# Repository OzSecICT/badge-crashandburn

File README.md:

# OzSec 2025 Badge: CRASHANDBURN
This is the git repo for the code and supporting documents for the OzSec 2025 badge, codename CRASHANDBURN.

This badge will be built in MicroPython on an RP2040 or RP2350, and support multiple minigames.

This repo is currently a work in progress as we start planning how to lay out the badge firmware.

## Contributing
You will need a few things to help develop the badge firmware:
- Visual Studio Code
- VS Code Extensions: Python, Pylance
- Python 3.12+
- mpremote 1.24+

Install Python, and then install `mpremote`. Install VS Code, and clone this repository. Open the repo in VS Code and install the recommended extensions.

Currently the badge firmware is developed with a Raspberry Pi Pico 2 on a breadboard. If you want to see the code, obtain one and follow these steps to get it setup:
- Plug in drive while holding BOOTSEL and use the flash script or VS Code Task to flash firmware. 
    - In VS Code, hit Ctrl+Shift+P or Cmd+Shift+P and choose `Tasks: Run Task` followed by `Flash MicroPython Firmware`.
- After you make changes to the code, hit Ctrl+Shift+B or Cmd+Shift+B to automatically upload the code and reset the device.

## Folder Structure
`.vscode` has the needed VS Code settings for recommended plugins, tasks, and settings for Pylance.

`firmware` has the MicroPython firmware, so everyone uses the same one.

`scripts` contains supporting scripts, such as flash and upload scripts. These are used by VS Code Tasks.

`source` is the MicroPython source files uploaded to the device.

`typings` contains Python typings for MicroPython. It stops the red squigglies.

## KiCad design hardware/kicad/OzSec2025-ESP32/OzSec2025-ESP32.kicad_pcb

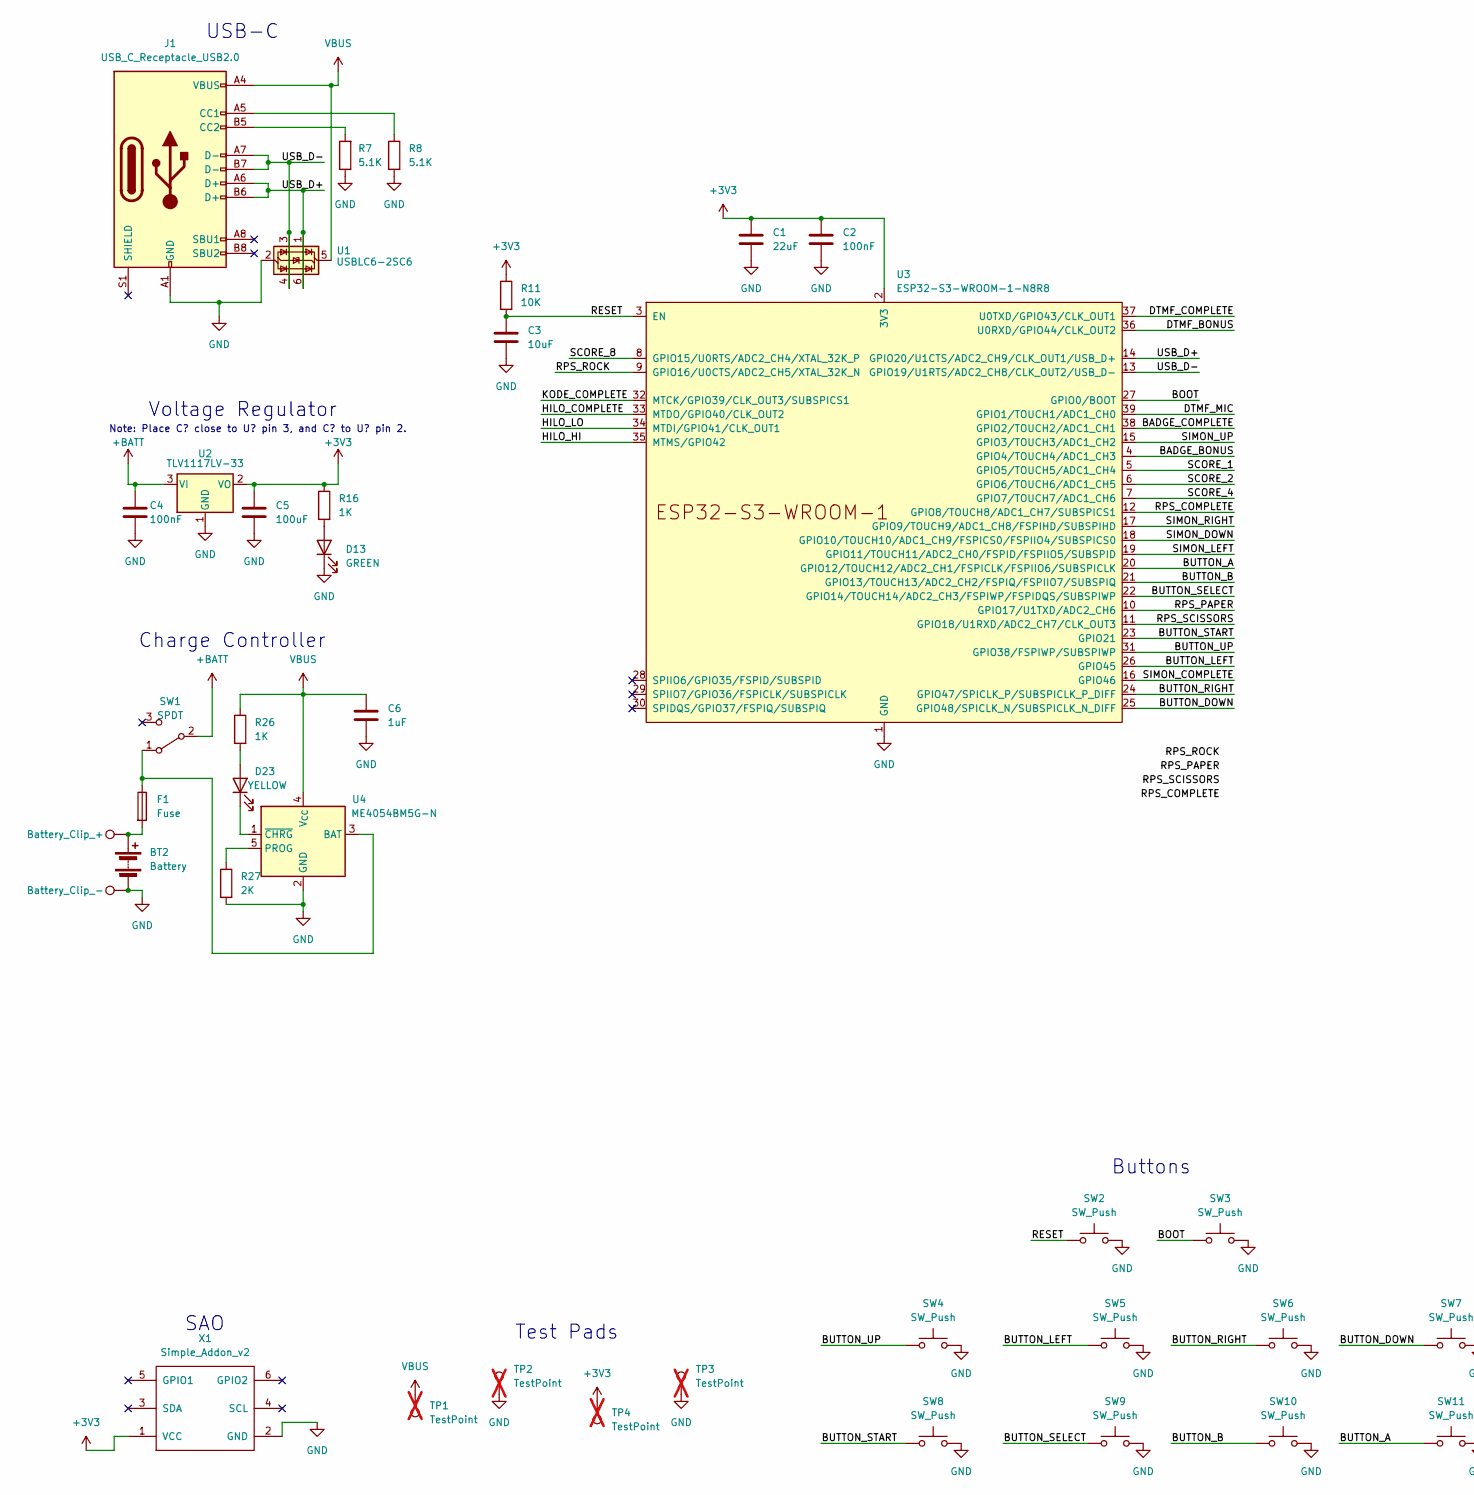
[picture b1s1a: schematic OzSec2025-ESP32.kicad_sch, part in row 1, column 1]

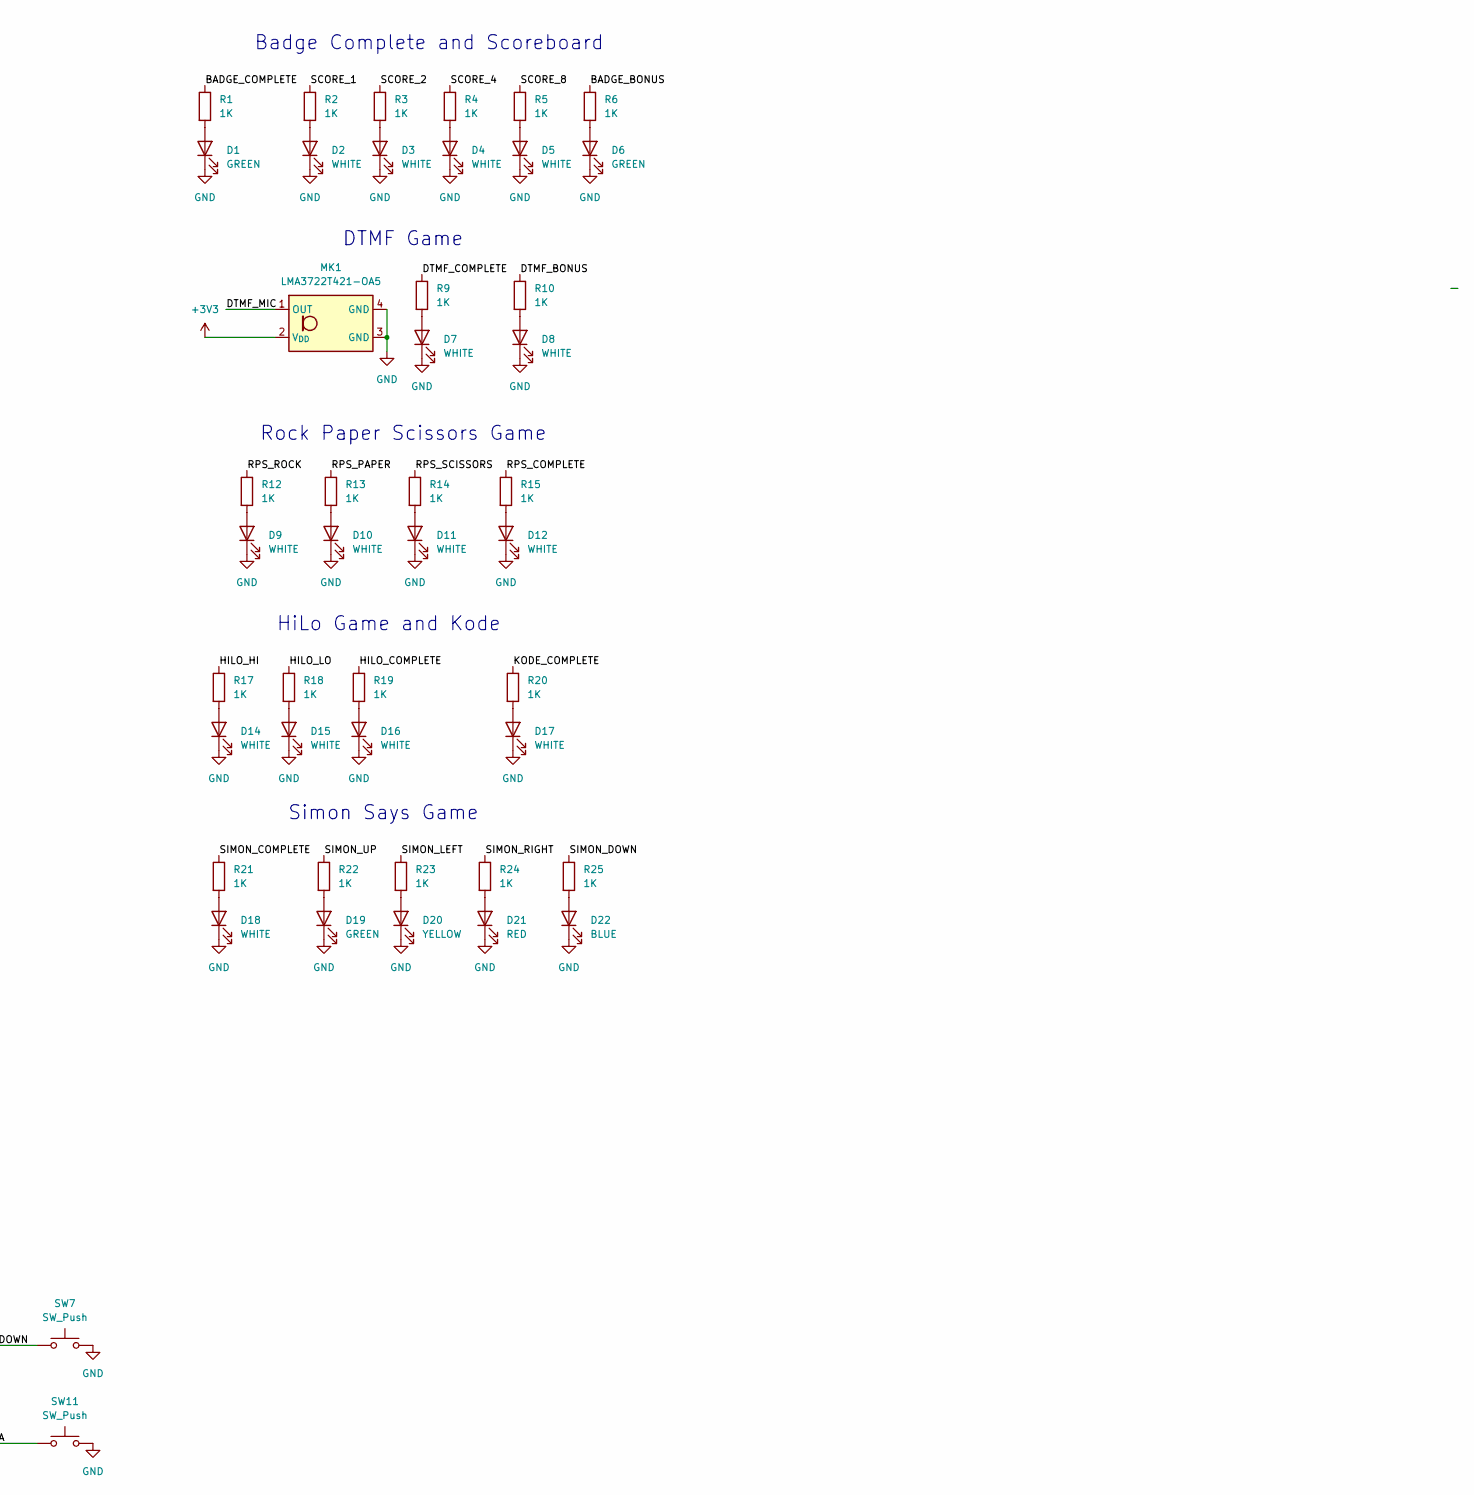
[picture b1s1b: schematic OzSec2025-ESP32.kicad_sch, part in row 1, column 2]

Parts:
BT1: Battery_Clip_+; MY-AA-04; LCSC C2979179
BT2: Battery; MY-AA-04; LCSC C2979179
BT3: Battery_Clip_-; MY-AA-04; LCSC C2979179
C1: 22uF; C_0805_2012Metric_Pad1.18x1.45mm_HandSolder; LCSC C45783
C2, C4: 100nF; C_0805_2012Metric_Pad1.18x1.45mm_HandSolder; LCSC C49678
C3: 10uF; C_0805_2012Metric_Pad1.18x1.45mm_HandSolder; LCSC C15850
C5: 100uF; C_1206_3216Metric_Pad1.33x1.80mm_HandSolder; LCSC C15008
C6: 1uF; C_0805_2012Metric_Pad1.18x1.45mm_HandSolder; LCSC C28323
D1, D6, D13, D19: GREEN; LED_0805_2012Metric_Pad1.15x1.40mm_HandSolder; LCSC C2297
D2, D3, D4, D5, D7, D8, D9, D10, D11, D12, D14, D15, D16, D17, D18: WHITE; LED_0805_2012Metric_Pad1.15x1.40mm_HandSolder; LCSC C34499
D20, D23: YELLOW; LED_0805_2012Metric_Pad1.15x1.40mm_HandSolder; LCSC C2296
D21: RED; LED_0805_2012Metric_Pad1.15x1.40mm_HandSolder; LCSC C84256
D22: BLUE; LED_0805_2012Metric_Pad1.15x1.40mm_HandSolder; LCSC C2293
F1: Fuse; Fuse_1206_3216Metric_Pad1.42x1.75mm_HandSolder; LCSC C261957
J1: USB_C_Receptacle_USB2.0; USB_C_Receptacle_G-Switch_GT-USB-7010ASV; LCSC C2988369
MK1: LMA3722T421-OA5; LCSC C5373233
R1, R2, R3, R4, R5, R6, R9, R10, R12, R13, R14, R15, R16, R17, R18, R19, R20, R21, R22, R23, R24, R25, R26: 1K; R_0805_2012Metric_Pad1.20x1.40mm_HandSolder; LCSC C17513
R7, R8: 5.1K; R_0805_2012Metric_Pad1.20x1.40mm_HandSolder; LCSC C27834
R11: 10K; R_0805_2012Metric_Pad1.20x1.40mm_HandSolder; LCSC C17414
R27: 2K; R_0805_2012Metric_Pad1.20x1.40mm_HandSolder; LCSC C17604
SW1: SPDT; SW_SPDT_PCM12; LCSC C431541
SW2, SW3, SW4, SW5, SW6, SW7, SW8, SW9, SW10, SW11: SW_Push; SW_Push_1P1T_XKB_TS-1187A; LCSC C318884
TP1, TP4: TestPoint; TestPoint_Pad_1.5x1.5mm; not fitted
TP2, TP3: TestPoint; TestPoint_Pad_D1.5mm; not fitted
U1: USBLC6-2SC6; SOT-23-6; LCSC C2827654
U2: TLV1117LV-33; SOT-223-3_TabPin2; LCSC C15578
U3: ESP32-S3-WROOM-1-N8R8; ESP32-S3-WROOM-1; LCSC C2913201
U4: ME4054BM5G-N; TSOT-23-5; LCSC C478383
X1: Simple_Addon_v2; Simple_Addon_v2-BADGE-2x3; LCSC C2935983

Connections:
+3V3: C1.1, C2.1, C5.1, MK1.2 (V_{DD}), R11.1, R16.1, TP4.1, U2.2 (VO), U3.2 (3V3), X1.1 (VCC)
+BATT: C4.1, SW1.2 (B), U2.3 (VI)
/BADGE_BONUS: R6.1, U3.4 (GPIO4/TOUCH4/ADC1_CH3)
/BADGE_COMPLETE: R1.1, U3.38 (GPIO2/TOUCH2/ADC1_CH1)
/BOOT: SW3.1, U3.27 (GPIO0/BOOT)
/BUTTON_A: SW11.1, U3.20 (GPIO12/TOUCH12/ADC2_CH1/FSPICLK/FSPIIO6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)
/BUTTON_B: SW10.1, U3.21 (GPIO13/TOUCH13/ADC2_CH2/FSPIQ/FSPIIO7/S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)
/BUTTON_DOWN: SW7.1, U3.25 (GPIO48/SPICLK_N/SUBSPICLK_N_DIFF)
/BUTTON_LEFT: SW5.1, U3.26 (GPIO45)
/BUTTON_RIGHT: SW6.1, U3.24 (GPIO47/SPICLK_P/SUBSPICLK_P_DIFF)
/BUTTON_SELECT: SW9.1, U3.22 (GPIO14/TOUCH14/ADC2_CH3/FSPIWP/FSPIDQS/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)
/BUTTON_START: SW8.1, U3.23 (GPIO21)
/BUTTON_UP: SW4.1, U3.31 (GPIO38/FSPIWP/SUBSPIWP)
/DTMF_BONUS: R10.1, U3.36 (U0RXD/GPIO44/CLK_OUT2)
/DTMF_COMPLETE: R9.1, U3.37 (U0TXD/GPIO43/CLK_OUT1)
/DTMF_MIC: MK1.1 (OUT), U3.39 (GPIO1/TOUCH1/ADC1_CH0)
/HILO_COMPLETE: R19.1, U3.33 (MTDO/GPIO40/CLK_OUT2)
/HILO_HI: R17.1, U3.35 (MTMS/GPIO42)
/HILO_LO: R18.1, U3.34 (MTDI/GPIO41/CLK_OUT1)
/KODE_COMPLETE: R20.1, U3.32 (MTCK/GPIO39/CLK_OUT3/SUBSPICS1)
/RESET: C3.1, R11.2, SW2.1, U3.3 (EN)
/RPS_COMPLETE: R15.1, U3.12 (GPIO8/TOUCH8/ADC1_CH7/SUBSPICS1)
/RPS_PAPER: R13.1, U3.10 (GPIO17/U1TXD/ADC2_CH6)
/RPS_ROCK: R12.1, U3.9 (GPIO16/U0CTS/ADC2_CH5/XTAL_32K_N)
/RPS_SCISSORS: R14.1, U3.11 (GPIO18/U1RXD/ADC2_CH7/CLK_OUT3)
/SCORE_1: R2.1, U3.5 (GPIO5/TOUCH5/ADC1_CH4)
/SCORE_2: R3.1, U3.6 (GPIO6/TOUCH6/ADC1_CH5)
/SCORE_4: R4.1, U3.7 (GPIO7/TOUCH7/ADC1_CH6)
/SCORE_8: R5.1, U3.8 (GPIO15/U0RTS/ADC2_CH4/XTAL_32K_P)
/SIMON_COMPLETE: R21.1, U3.16 (GPIO46)
/SIMON_DOWN: R25.1, U3.18 (GPIO10/TOUCH10/ADC1_CH9/FSPICS0/FSPIIO4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)
/SIMON_LEFT: R23.1, U3.19 (GPIO11/TOUCH11/ADC2_CH0/FSPID/FSPIIO5/S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)
/SIMON_RIGHT: R24.1, U3.17 (GPIO9/TOUCH9/ADC1_CH8/FSPIHD/SUBSPIHD)
/SIMON_UP: R22.1, U3.15 (GPIO3/TOUCH3/ADC1_CH2)
/USB_D+: J1.A6 (D+), J1.B6 (D+), U1.1 (I/O1), U1.6 (I/O1), U3.14 (GPIO20/U1CTS/ADC2_CH9/CLK_OUT1/USB_D+)
/USB_D-: J1.A7 (D-), J1.B7 (D-), U1.3 (I/O2), U1.4 (I/O2), U3.13 (GPIO19/U1RTS/ADC2_CH8/CLK_OUT2/USB_D-)
GND: BT1.2, BT3.1, C1.2, C2.2, C3.2, C4.2, C5.2, C6.2, D1.1 (K), D2.1 (K), D3.1 (K), D4.1 (K), D5.1 (K), D6.1 (K), D7.1 (K), D8.1 (K), D9.1 (K), D10.1 (K), D11.1 (K), D12.1 (K), D13.1 (K), D14.1 (K), D15.1 (K), D16.1 (K), D17.1 (K), D18.1 (K), D19.1 (K), D20.1 (K), D21.1 (K), D22.1 (K), J1.A1 (GND), J1.A12 (GND), J1.B1 (GND), J1.B12 (GND), MK1.3 (GND), MK1.4 (GND), R7.1, R8.2, R27.2, SW2.2, SW3.2, SW4.2, SW5.2, SW6.2, SW7.2, SW8.2, SW9.2, SW10.2, SW11.2, TP2.1, TP3.1, U1.2 (GND), U2.1 (GND), U3.1 (GND), U3.40 (GND), U3.41 (GND), U4.2 (GND), X1.2 (GND)
unnamed: BT1.1, F1.2
unnamed: D1.2 (A), R1.2
unnamed: D2.2 (A), R2.2
unnamed: D3.2 (A), R3.2
unnamed: D4.2 (A), R4.2
unnamed: D5.2 (A), R5.2
unnamed: D6.2 (A), R6.2
unnamed: D7.2 (A), R9.2
unnamed: D8.2 (A), R10.2
unnamed: D9.2 (A), R12.2
unnamed: D10.2 (A), R13.2
unnamed: D11.2 (A), R14.2
unnamed: D12.2 (A), R15.2
unnamed: D13.2 (A), R16.2
unnamed: D14.2 (A), R17.2
unnamed: D15.2 (A), R18.2
unnamed: D16.2 (A), R19.2
unnamed: D17.2 (A), R20.2
unnamed: D18.2 (A), R21.2
unnamed: D19.2 (A), R22.2
unnamed: D20.2 (A), R23.2
unnamed: D21.2 (A), R24.2
unnamed: D22.2 (A), R25.2
unnamed: D23.2 (A), R26.2
unnamed: D23.1 (K), U4.1 (~CHRG)
unnamed: J1.A5 (CC1), R8.1
unnamed: J1.B5 (CC2), R7.2
unnamed: F1.1, SW1.1 (A), U4.3 (BAT)
unnamed: R27.1, U4.5 (PROG)
VBUS: C6.1, J1.A4 (VBUS), J1.A9 (VBUS), J1.B4 (VBUS), J1.B9 (VBUS), R26.1, TP1.1, U1.5 (VBUS), U4.4 (V_{CC})

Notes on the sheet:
USB-C
Charge Controller
Badge Complete and Scoreboard
Test Pads
DTMF Game
Voltage Regulator
SAO
HiLo Game and Kode
Note: Place C? close to U? pin 3, and C? to U? pin 2.
Buttons
Simon Says Game
Rock Paper Scissors Game

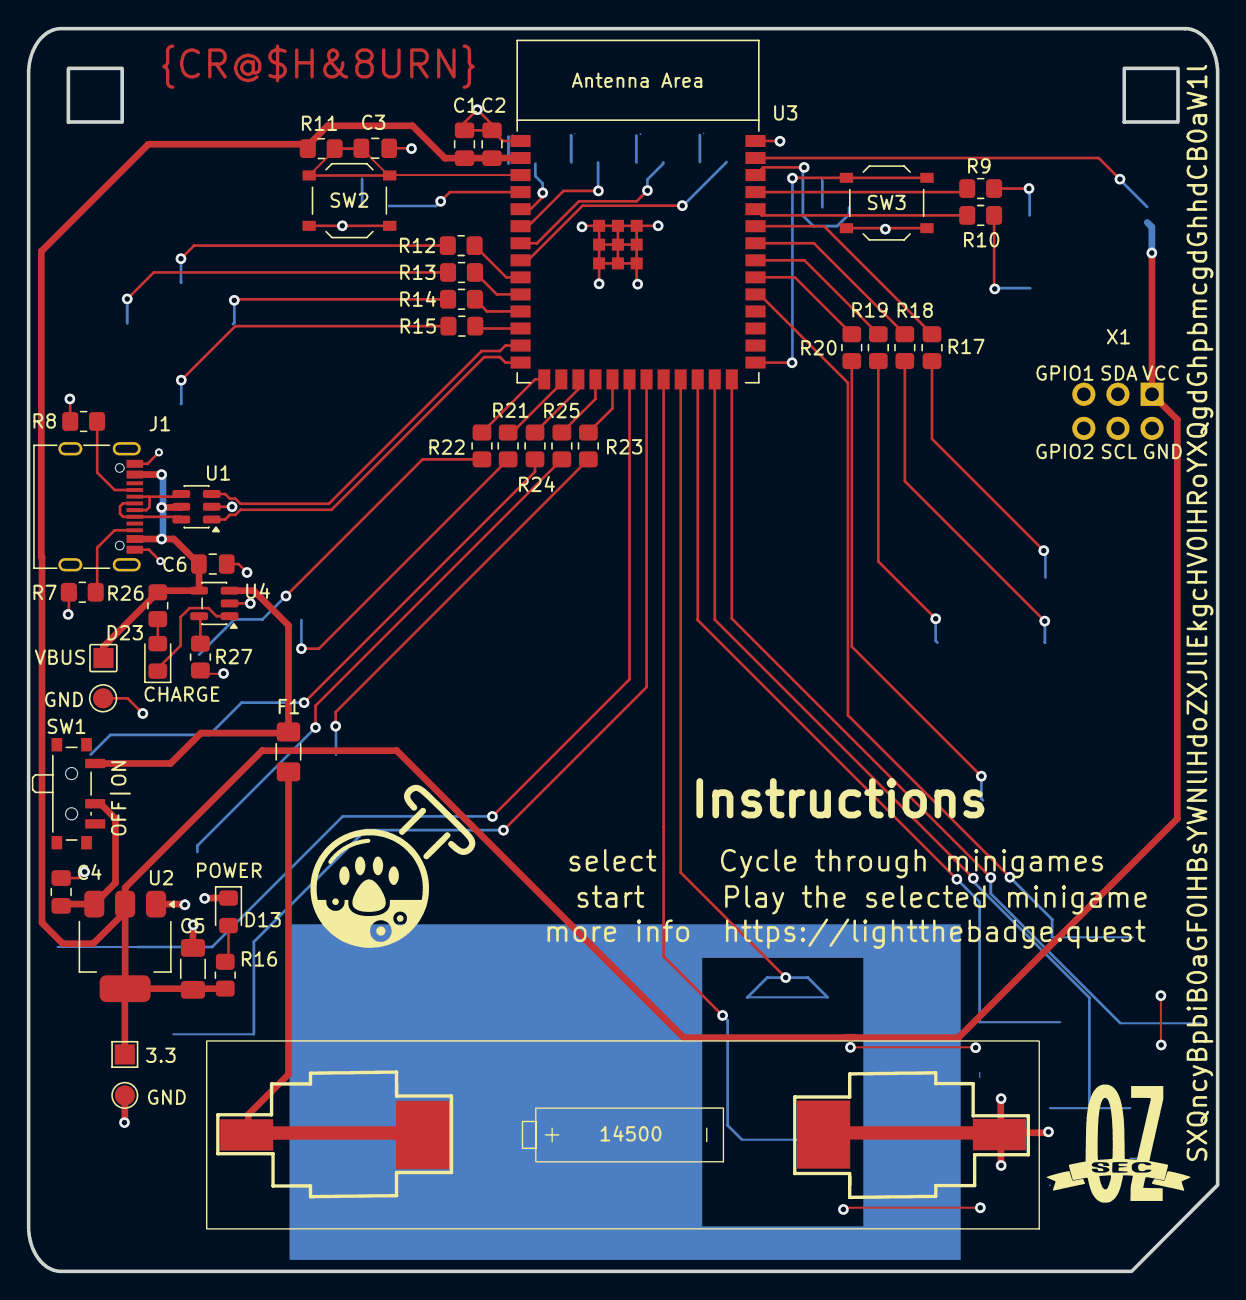
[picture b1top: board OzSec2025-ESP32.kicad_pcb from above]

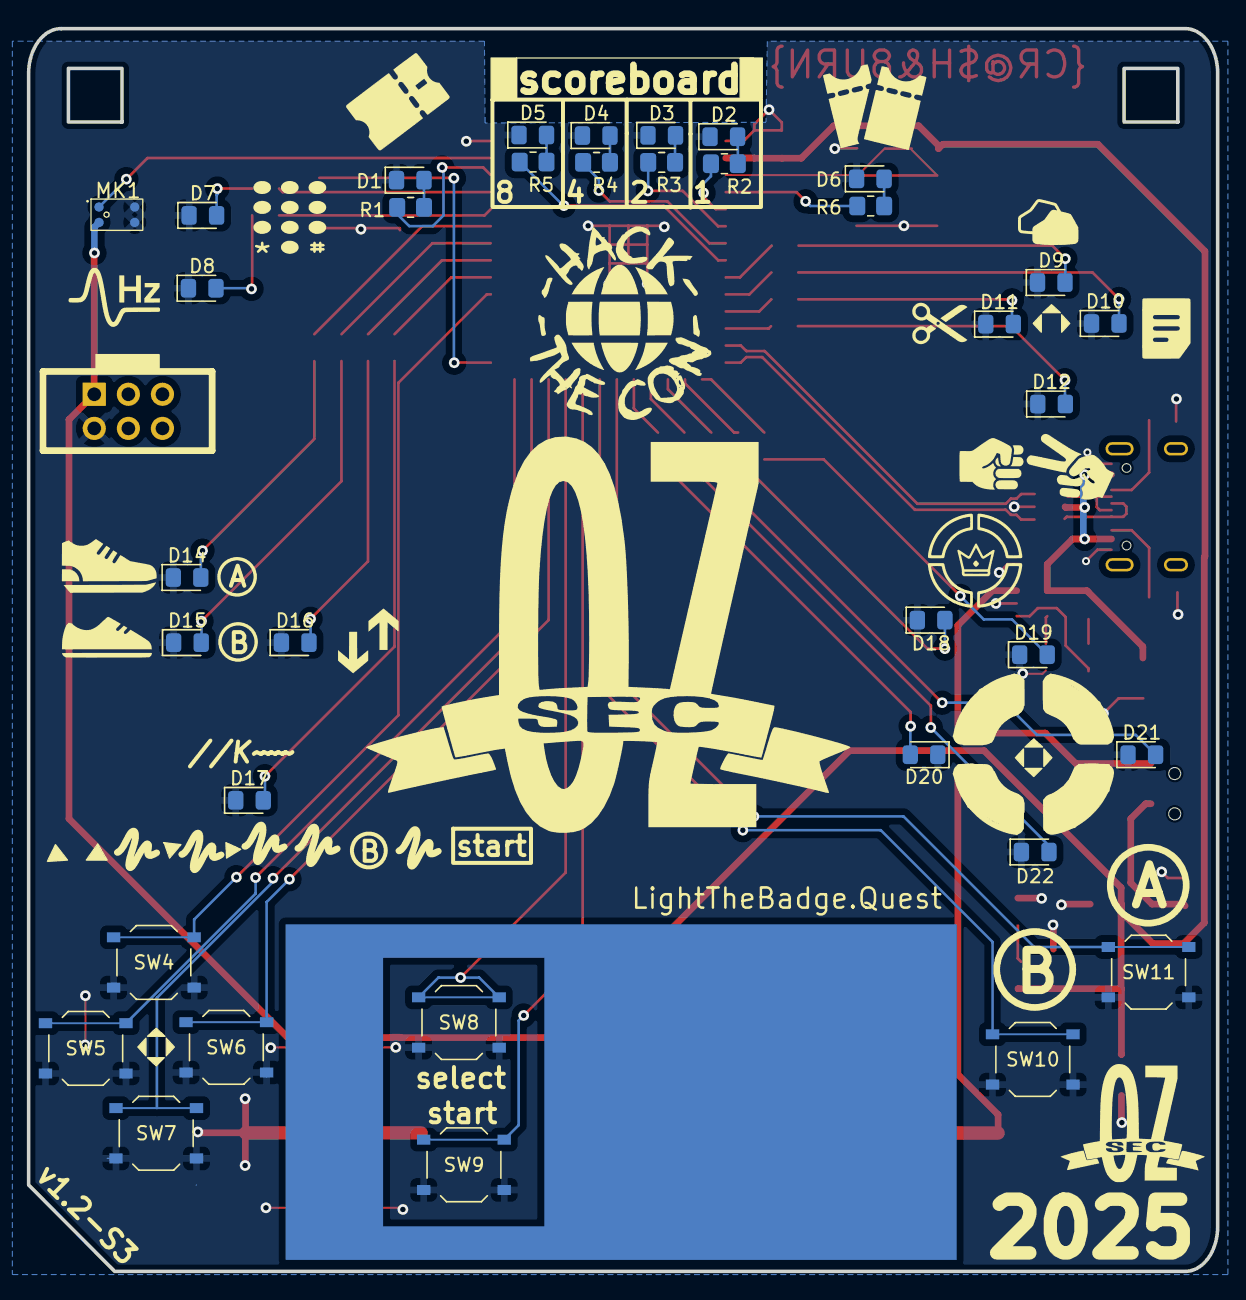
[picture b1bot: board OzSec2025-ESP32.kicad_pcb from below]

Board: 2 copper layers, 88.6 x 92.6 mm, 82 parts (37 on the bottom side), 67 nets.

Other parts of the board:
BATTERY: Battery; MY-AA-04_Silkscreen_Only

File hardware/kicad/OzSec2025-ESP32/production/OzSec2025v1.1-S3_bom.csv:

Designator,Footprint,Quantity,Value,LCSC Part #
BATTERY,MY-AA-04_Silkscreen_Only,1,Battery,C2979179
BT1,MY-AA-04,1,Battery_Clip_+,C2979179
BT3,MY-AA-04,1,Battery_Clip_-,C2979179
C1,0805,1,22uF,C45783
"C2, C4",0805,2,100nF,C49678
C3,0805,1,10uF,C15850
C5,1206,1,100uF,C15008
C6,0805,1,1uF,C28323
"D1, D13, D19, D6",0805,4,GREEN,C2297
"D10, D11, D12, D14, D15, D16, D17, D18, D2, D3, D4, D5, D7, D8, D9",0805,15,WHITE,C34499
"D20, D23",0805,2,YELLOW,C2296
D21,0805,1,RED,C84256
D22,0805,1,BLUE,C2293
F1,1206,1,Fuse,C261957
J1,USB_C_Receptacle_G-Switch_GT-USB-7010ASV,1,USB_C_Receptacle_USB2.0,C2988369
MK1,LMA3722T421-OA5,1,LMA3722T421-OA5,C5373233
"R1, R10, R12, R13, R14, R15, R16, R17, R18, R19, R2, R20, R21, R22, R23, R24, R25, R26, R3, R4, R5, R6, R9",0805,23,1K,C17513
R11,0805,1,10K,C17414
R27,0805,1,2K,C17604
"R7, R8",0805,2,5.1K,C27834
SW1,SW_SPDT_PCM12,1,SPDT,C431541
"SW10, SW11, SW2, SW3, SW4, SW5, SW6, SW7, SW8, SW9",SW_Push_1P1T_XKB_TS-1187A,10,SW_Push,C318884
U1,SOT-23-6,1,USBLC6-2SC6,C2827654
U2,SOT-223-3_TabPin2,1,TLV1117LV-33,C15578
U3,ESP32-S3-WROOM-1,1,ESP32-S3-WROOM-1-N8R8,C2913201
U4,TSOT-23-5,1,ME4054BM5G-N,C478383
X1,Simple_Addon_v2-BADGE-2x3,1,Simple_Addon_v2,C2935983

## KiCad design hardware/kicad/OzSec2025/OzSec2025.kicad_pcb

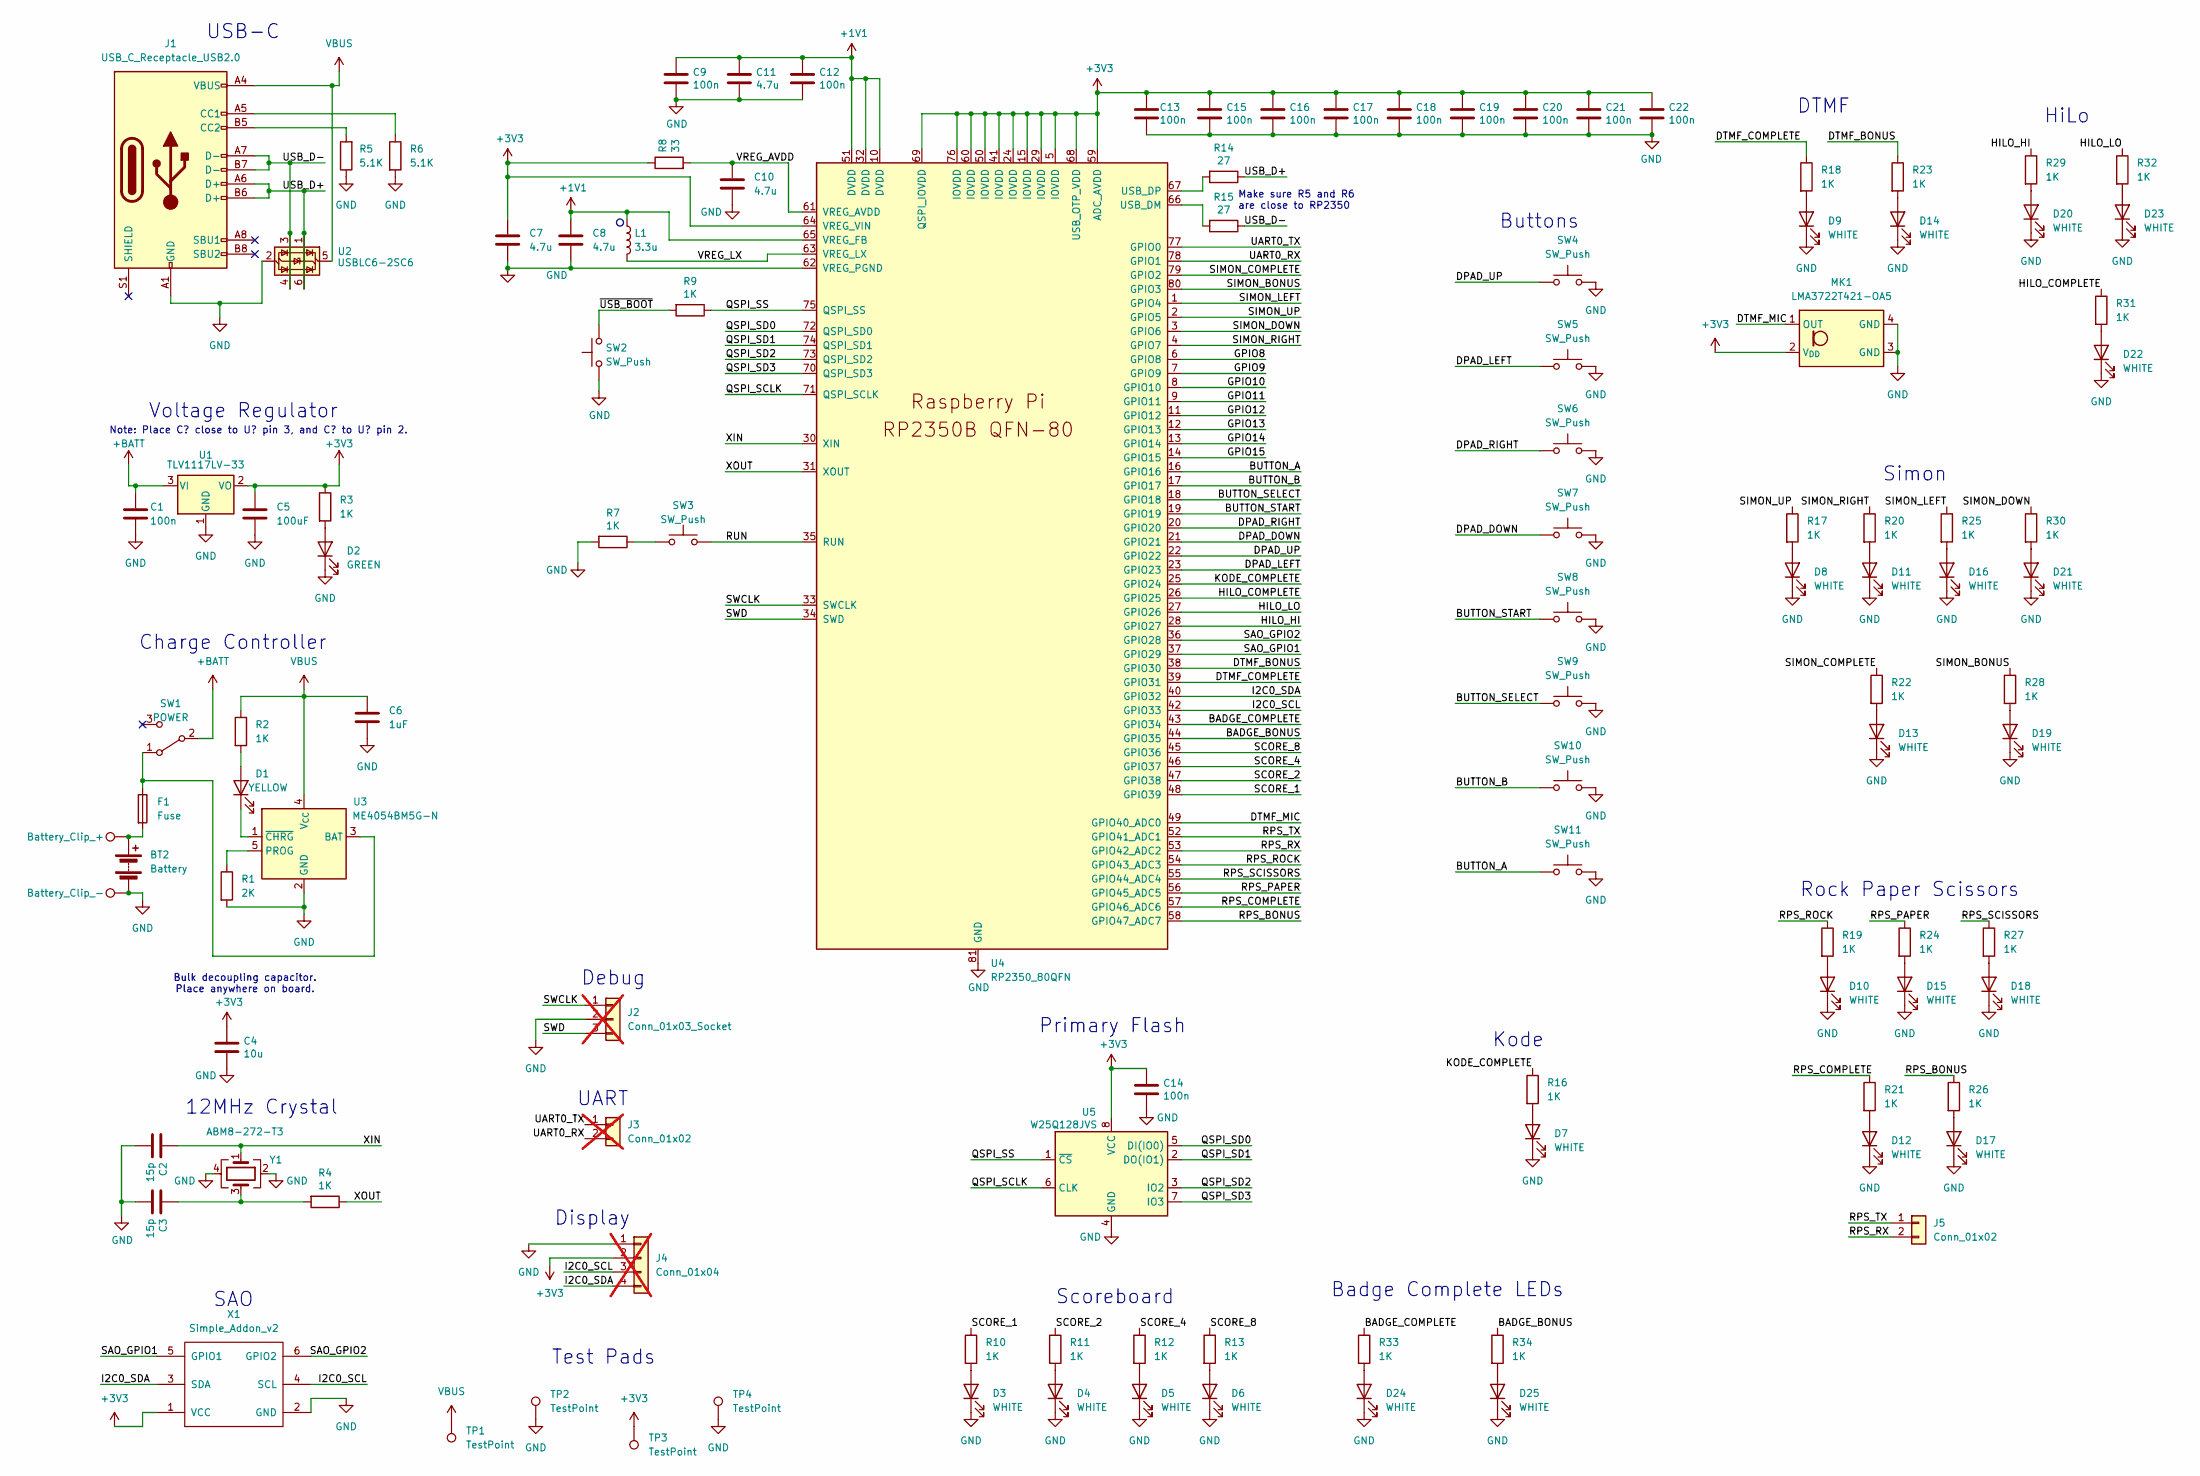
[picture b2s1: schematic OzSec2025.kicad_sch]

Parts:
BT1: Battery_Clip_+; MY-AA-04_BT1A
BT2: Battery; MY-AA-04; LCSC C2979179
BT3: Battery_Clip_-; MY-AA-04_BT1B
C1, C9, C12, C13, C14, C15, C16, C17, C18, C19, C20, C21, C22: 100n; C_0402_1005Metric; LCSC C1525
C2, C3: 15p; C_0402_1005Metric; LCSC C1548
C4: 10u; C_0805_2012Metric; LCSC C15850
C5: 100uF; C_1206_3216Metric; LCSC C15008
C6: 1uF; C_0402_1005Metric; LCSC C52923
C7, C8: 4.7u; C_0402_1005Metric_small_pads; LCSC C23733
C10, C11: 4.7u; C_0402_1005Metric; LCSC C23733
D1: YELLOW; LED_0805_2012Metric; LCSC C2296
D2: GREEN; LED_0805_2012Metric; LCSC C2297
D3, D4, D5, D6, D7, D8, D9, D10, D11, D12, D13, D14, D15, D16, D17, D18, D19, D20, D21, D22, D23, D24, D25: WHITE; LED_0805_2012Metric; LCSC C34499
F1: Fuse; Fuse_1206_3216Metric; LCSC C261957
J1: USB_C_Receptacle_USB2.0; USB_C_Receptacle_G-Switch_GT-USB-7010ASV; LCSC C2988369
J2: Conn_01x03_Socket; PinHeader_1x03_P2.54mm_Vertical; not fitted
J3: Conn_01x02; PinHeader_1x02_P2.54mm_Vertical; not fitted
J4: Conn_01x04; PinHeader_1x04_P2.54mm_Vertical; not fitted
J5: Conn_01x02; PinHeader_1x02_P2.54mm_Horizontal; LCSC C492410
L1: 3.3u; L_pol_2016; LCSC C42411119
MK1: LMA3722T421-OA5; LCSC C5373233
R1: 2K; R_0402_1005Metric; LCSC C4109
R2, R3, R4, R7, R9, R10, R11, R12, R13, R16, R17, R18, R19, R20, R21, R22, R23, R24, R25, R26, R27, R28, R29, R30, R31, R32, R33, R34: 1K; R_0402_1005Metric; LCSC C11702
R5, R6: 5.1K; R_0402_1005Metric; LCSC C25905
R8: 33; R_0402_1005Metric; LCSC C25105
R14, R15: 27; R_0402_1005Metric; LCSC C25100
SW1: POWER; SW_SPDT_PCM12; LCSC C431541
SW2, SW3, SW4, SW5, SW6, SW7, SW8, SW9, SW10, SW11: SW_Push; SW_Push_1P1T_XKB_TS-1187A; LCSC C318884
TP1, TP3: TestPoint; TestPoint_Pad_1.5x1.5mm
TP2, TP4: TestPoint; TestPoint_Pad_D1.5mm
U1: TLV1117LV-33; SOT-223-3_TabPin2; LCSC C15578
U2: USBLC6-2SC6; SOT-23-6; LCSC C2827654
U3: ME4054BM5G-N; TSOT-23-5; LCSC C478383
U4: RP2350_80QFN; RP2350-QFN-80-1EP_10x10_P0.4mm_EP3.4x3.4mm_ThermalVias; LCSC C42415655
U5: W25Q128JVS; SOIC-8_5.23x5.23mm_P1.27mm; LCSC C97521
X1: Simple_Addon_v2; Simple_Addon_v2-BADGE-2x3; LCSC C2935983
Y1: ABM8-272-T3; Crystal_SMD_3225-4Pin_3.2x2.5mm; LCSC C20625731

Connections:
+1V1: C8.1, C9.1, C11.1, C12.1, L1.1, U4.10 (DVDD), U4.32 (DVDD), U4.51 (DVDD), U4.65 (VREG_FB)
+3V3: C4.1, C5.1, C7.1, C13.1, C14.1, C15.1, C16.1, C17.1, C18.1, C19.1, C20.1, C21.1, C22.1, J4.2, MK1.2 (V_{DD}), R3.1, R8.1, TP3.1, U1.2 (VO), U4.5 (IOVDD), U4.15 (IOVDD), U4.24 (IOVDD), U4.29 (IOVDD), U4.41 (IOVDD), U4.50 (IOVDD), U4.59 (ADC_AVDD), U4.60 (IOVDD), U4.64 (VREG_VIN), U4.68 (USB_OTP_VDD), U4.69 (QSPI_IOVDD), U4.76 (IOVDD), U5.8 (VCC), X1.1 (VCC)
+BATT: C1.1, SW1.2 (B), U1.3 (VI)
/BADGE_BONUS: R34.1, U4.44 (GPIO35)
/BADGE_COMPLETE: R33.1, U4.43 (GPIO34)
/BUTTON_A: SW11.1, U4.16 (GPIO16)
/BUTTON_B: SW10.1, U4.17 (GPIO17)
/BUTTON_SELECT: SW9.1, U4.18 (GPIO18)
/BUTTON_START: SW8.1, U4.19 (GPIO19)
/DPAD_DOWN: SW7.1, U4.21 (GPIO21)
/DPAD_LEFT: SW5.1, U4.23 (GPIO23)
/DPAD_RIGHT: SW6.1, U4.20 (GPIO20)
/DPAD_UP: SW4.1, U4.22 (GPIO22)
/DTMF_BONUS: R23.1, U4.38 (GPIO30)
/DTMF_COMPLETE: R18.1, U4.39 (GPIO31)
/DTMF_MIC: MK1.1 (OUT), U4.49 (GPIO40_ADC0)
/GPIO8: U4.6 (GPIO8)
/GPIO9: U4.7 (GPIO9)
/GPIO10: U4.8 (GPIO10)
/GPIO11: U4.9 (GPIO11)
/GPIO12: U4.11 (GPIO12)
/GPIO13: U4.12 (GPIO13)
/GPIO14: U4.13 (GPIO14)
/GPIO15: U4.14 (GPIO15)
/HILO_COMPLETE: R31.1, U4.26 (GPIO25)
/HILO_HI: R29.1, U4.28 (GPIO27)
/HILO_LO: R32.1, U4.27 (GPIO26)
/I2C0_SCL: J4.3, U4.42 (GPIO33), X1.4 (SCL)
/I2C0_SDA: J4.4, U4.40 (GPIO32), X1.3 (SDA)
/KODE_COMPLETE: R16.1, U4.25 (GPIO24)
/QSPI_SCLK: U4.71 (QSPI_SCLK), U5.6 (CLK)
/QSPI_SD0: U4.72 (QSPI_SD0), U5.5 (DI(IO0))
/QSPI_SD1: U4.74 (QSPI_SD1), U5.2 (DO(IO1))
/QSPI_SD2: U4.73 (QSPI_SD2), U5.3 (IO2)
/QSPI_SD3: U4.70 (QSPI_SD3), U5.7 (IO3)
/QSPI_SS: R9.1, U4.75 (QSPI_SS), U5.1 (~CS)
/RPS_BONUS: R26.1, U4.58 (GPIO47_ADC7)
/RPS_COMPLETE: R21.1, U4.57 (GPIO46_ADC6)
/RPS_PAPER: R24.1, U4.56 (GPIO45_ADC5)
/RPS_ROCK: R19.1, U4.54 (GPIO43_ADC3)
/RPS_RX: J5.2, U4.53 (GPIO42_ADC2)
/RPS_SCISSORS: R27.1, U4.55 (GPIO44_ADC4)
/RPS_TX: J5.1, U4.52 (GPIO41_ADC1)
/RUN: SW3.2, U4.35 (RUN)
/SAO_GPIO1: U4.37 (GPIO29), X1.5 (GPIO1)
/SAO_GPIO2: U4.36 (GPIO28), X1.6 (GPIO2)
/SCORE_1: R10.1, U4.48 (GPIO39)
/SCORE_2: R11.1, U4.47 (GPIO38)
/SCORE_4: R12.1, U4.46 (GPIO37)
/SCORE_8: R13.1, U4.45 (GPIO36)
/SIMON_BONUS: R28.1, U4.80 (GPIO3)
/SIMON_COMPLETE: R22.1, U4.79 (GPIO2)
/SIMON_DOWN: R30.1, U4.3 (GPIO6)
/SIMON_LEFT: R25.1, U4.1 (GPIO4)
/SIMON_RIGHT: R20.1, U4.4 (GPIO7)
/SIMON_UP: R17.1, U4.2 (GPIO5)
/SWCLK: J2.1, U4.33 (SWCLK)
/SWD: J2.3, U4.34 (SWD)
/UART0_RX: J3.2, U4.78 (GPIO1)
/UART0_TX: J3.1, U4.77 (GPIO0)
/USB_D+: J1.A6 (D+), J1.B6 (D+), R14.1, U2.1 (I/O1), U2.6 (I/O1)
/USB_D-: J1.A7 (D-), J1.B7 (D-), R15.1, U2.3 (I/O2), U2.4 (I/O2)
/VREG_AVDD: C10.1, R8.2, U4.61 (VREG_AVDD)
/VREG_LX: L1.2, U4.63 (VREG_LX)
/XIN: C2.1, U4.30 (XIN), Y1.1
/XOUT: R4.1, U4.31 (XOUT)
/~USB_BOOT: R9.2, SW2.2
GND: BT2.2 (-), BT3.1, C1.2, C2.2, C3.2, C4.2, C5.2, C6.2, C7.2, C8.2, C9.2, C10.2, C11.2, C12.2, C13.2, C14.2, C15.2, C16.2, C17.2, C18.2, C19.2, C20.2, C21.2, C22.2, D2.1 (K), D3.1 (K), D4.1 (K), D5.1 (K), D6.1 (K), D7.1 (K), D8.1 (K), D9.1 (K), D10.1 (K), D11.1 (K), D12.1 (K), D13.1 (K), D14.1 (K), D15.1 (K), D16.1 (K), D17.1 (K), D18.1 (K), D19.1 (K), D20.1 (K), D21.1 (K), D22.1 (K), D23.1 (K), D24.1 (K), D25.1 (K), J1.A1 (GND), J1.A12 (GND), J1.B1 (GND), J1.B12 (GND), J2.2, J4.1, MK1.3 (GND), MK1.4 (GND), R1.2, R5.1, R6.2, R7.2, SW2.1, SW4.2, SW5.2, SW6.2, SW7.2, SW8.2, SW9.2, SW10.2, SW11.2, TP2.1, TP4.1, U1.1 (GND), U2.2 (GND), U3.2 (GND), U4.62 (VREG_PGND), U4.81 (GND), U5.4 (GND), X1.2 (GND), Y1.2, Y1.4
unnamed: BT1.1, BT2.1 (+), F1.2
unnamed: C3.1, R4.2, Y1.3
unnamed: D1.2 (A), R2.2
unnamed: D1.1 (K), U3.1 (~CHRG)
unnamed: D2.2 (A), R3.2
unnamed: D3.2 (A), R10.2
unnamed: D4.2 (A), R11.2
unnamed: D5.2 (A), R12.2
unnamed: D6.2 (A), R13.2
unnamed: D7.2 (A), R16.2
unnamed: D8.2 (A), R17.2
unnamed: D9.2 (A), R18.2
unnamed: D10.2 (A), R19.2
unnamed: D11.2 (A), R20.2
unnamed: D12.2 (A), R21.2
unnamed: D13.2 (A), R22.2
unnamed: D14.2 (A), R23.2
unnamed: D15.2 (A), R24.2
unnamed: D16.2 (A), R25.2
unnamed: D17.2 (A), R26.2
unnamed: D18.2 (A), R27.2
unnamed: D19.2 (A), R28.2
unnamed: D20.2 (A), R29.2
unnamed: D21.2 (A), R30.2
unnamed: D22.2 (A), R31.2
unnamed: D23.2 (A), R32.2
unnamed: D24.2 (A), R33.2
unnamed: D25.2 (A), R34.2
unnamed: J1.A5 (CC1), R6.1
unnamed: J1.B5 (CC2), R5.2
unnamed: R7.1, SW3.1
unnamed: F1.1, SW1.1 (A), U3.3 (BAT)
unnamed: R1.1, U3.5 (PROG)
unnamed: R15.2, U4.66 (USB_DM)
unnamed: R14.2, U4.67 (USB_DP)
VBUS: C6.1, J1.A4 (VBUS), J1.A9 (VBUS), J1.B4 (VBUS), J1.B9 (VBUS), R2.1, TP1.1, U2.5 (VBUS), U3.4 (V_{CC})

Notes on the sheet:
Primary Flash
USB-C
12MHz Crystal
UART
Buttons
Charge Controller
Test Pads
HiLo
Badge Complete LEDs
Simon
Display
Bulk decoupling capacitor. Place anywhere on board.
DTMF
Debug
Voltage Regulator
SAO
Kode
Note: Place C? close to U? pin 3, and C? to U? pin 2.
Make sure R5 and R6 are close to RP2350
Scoreboard
Rock Paper Scissors
